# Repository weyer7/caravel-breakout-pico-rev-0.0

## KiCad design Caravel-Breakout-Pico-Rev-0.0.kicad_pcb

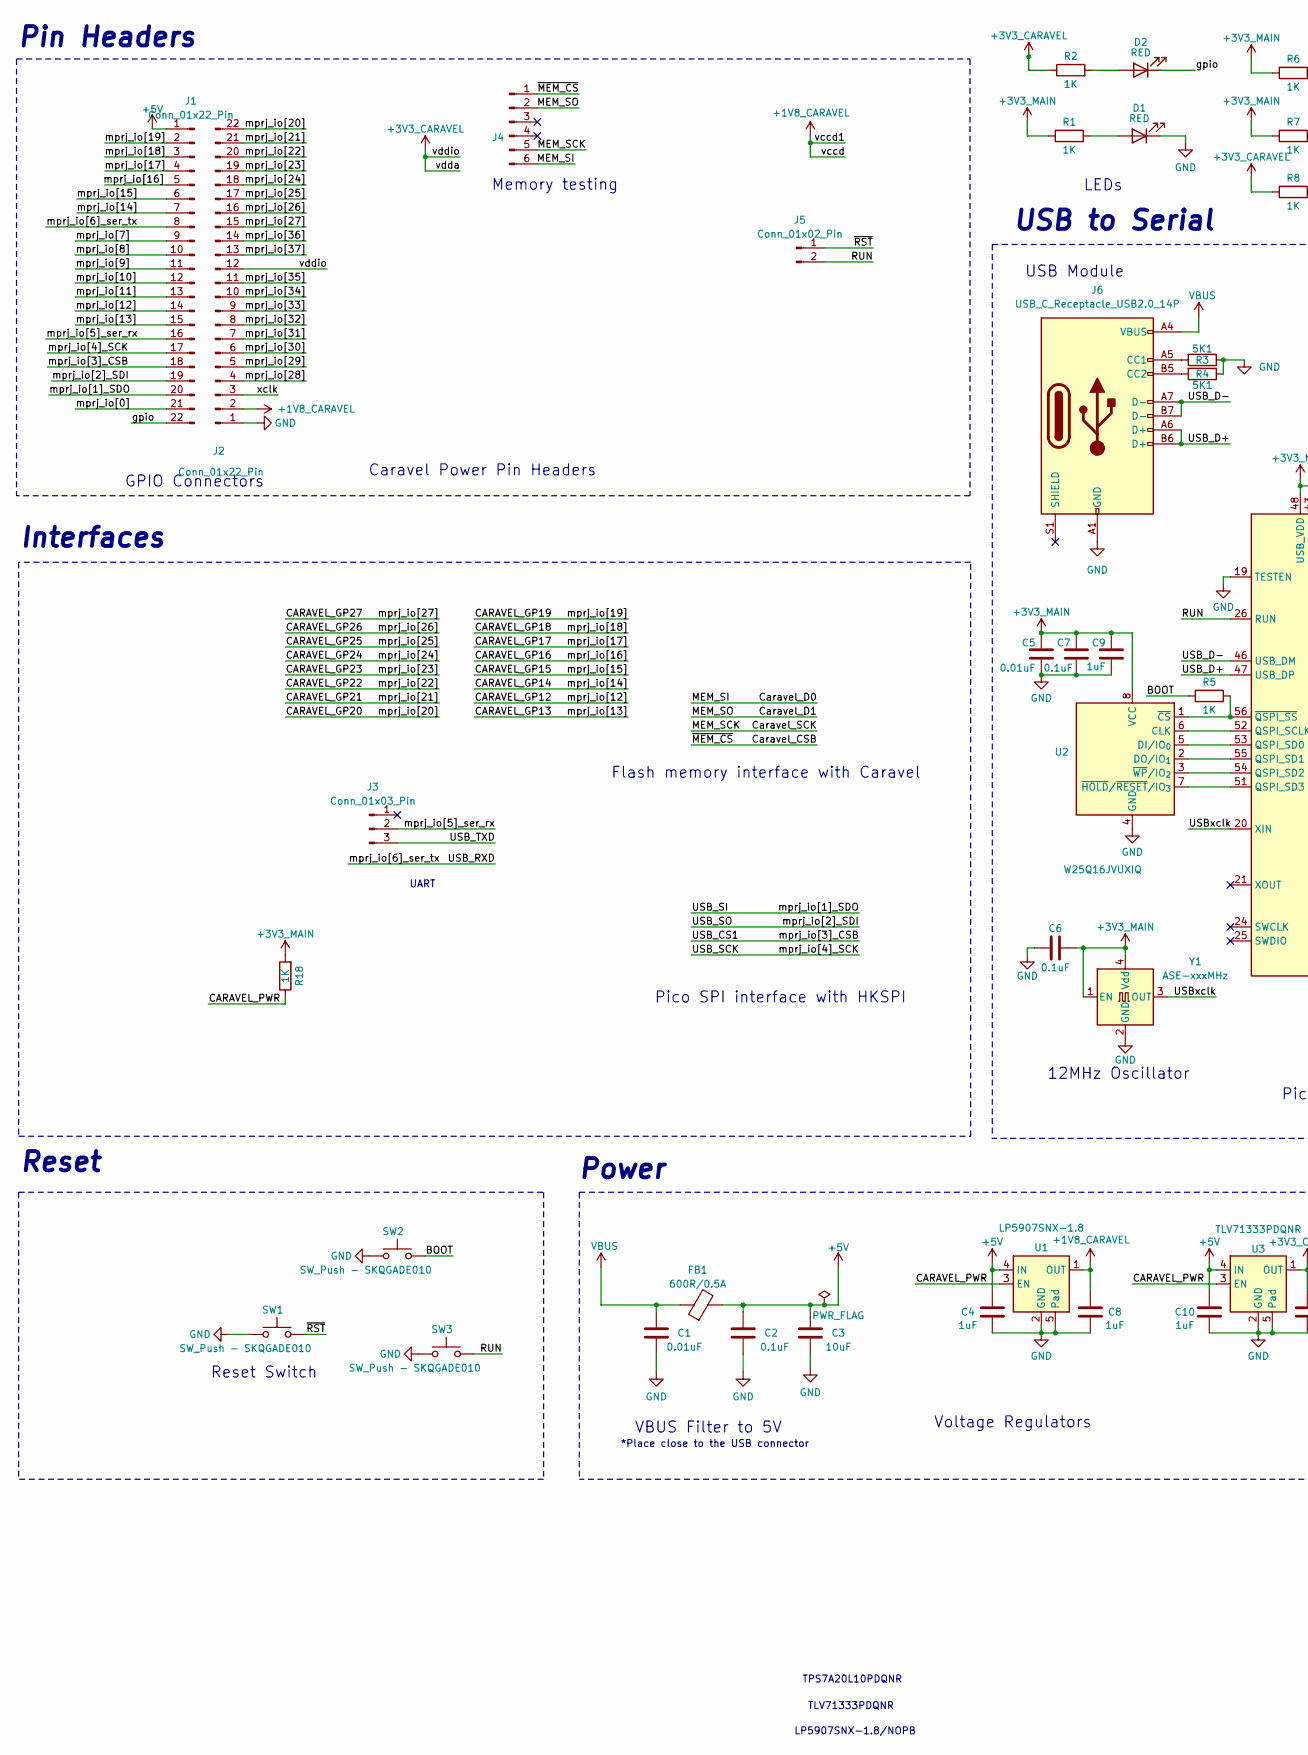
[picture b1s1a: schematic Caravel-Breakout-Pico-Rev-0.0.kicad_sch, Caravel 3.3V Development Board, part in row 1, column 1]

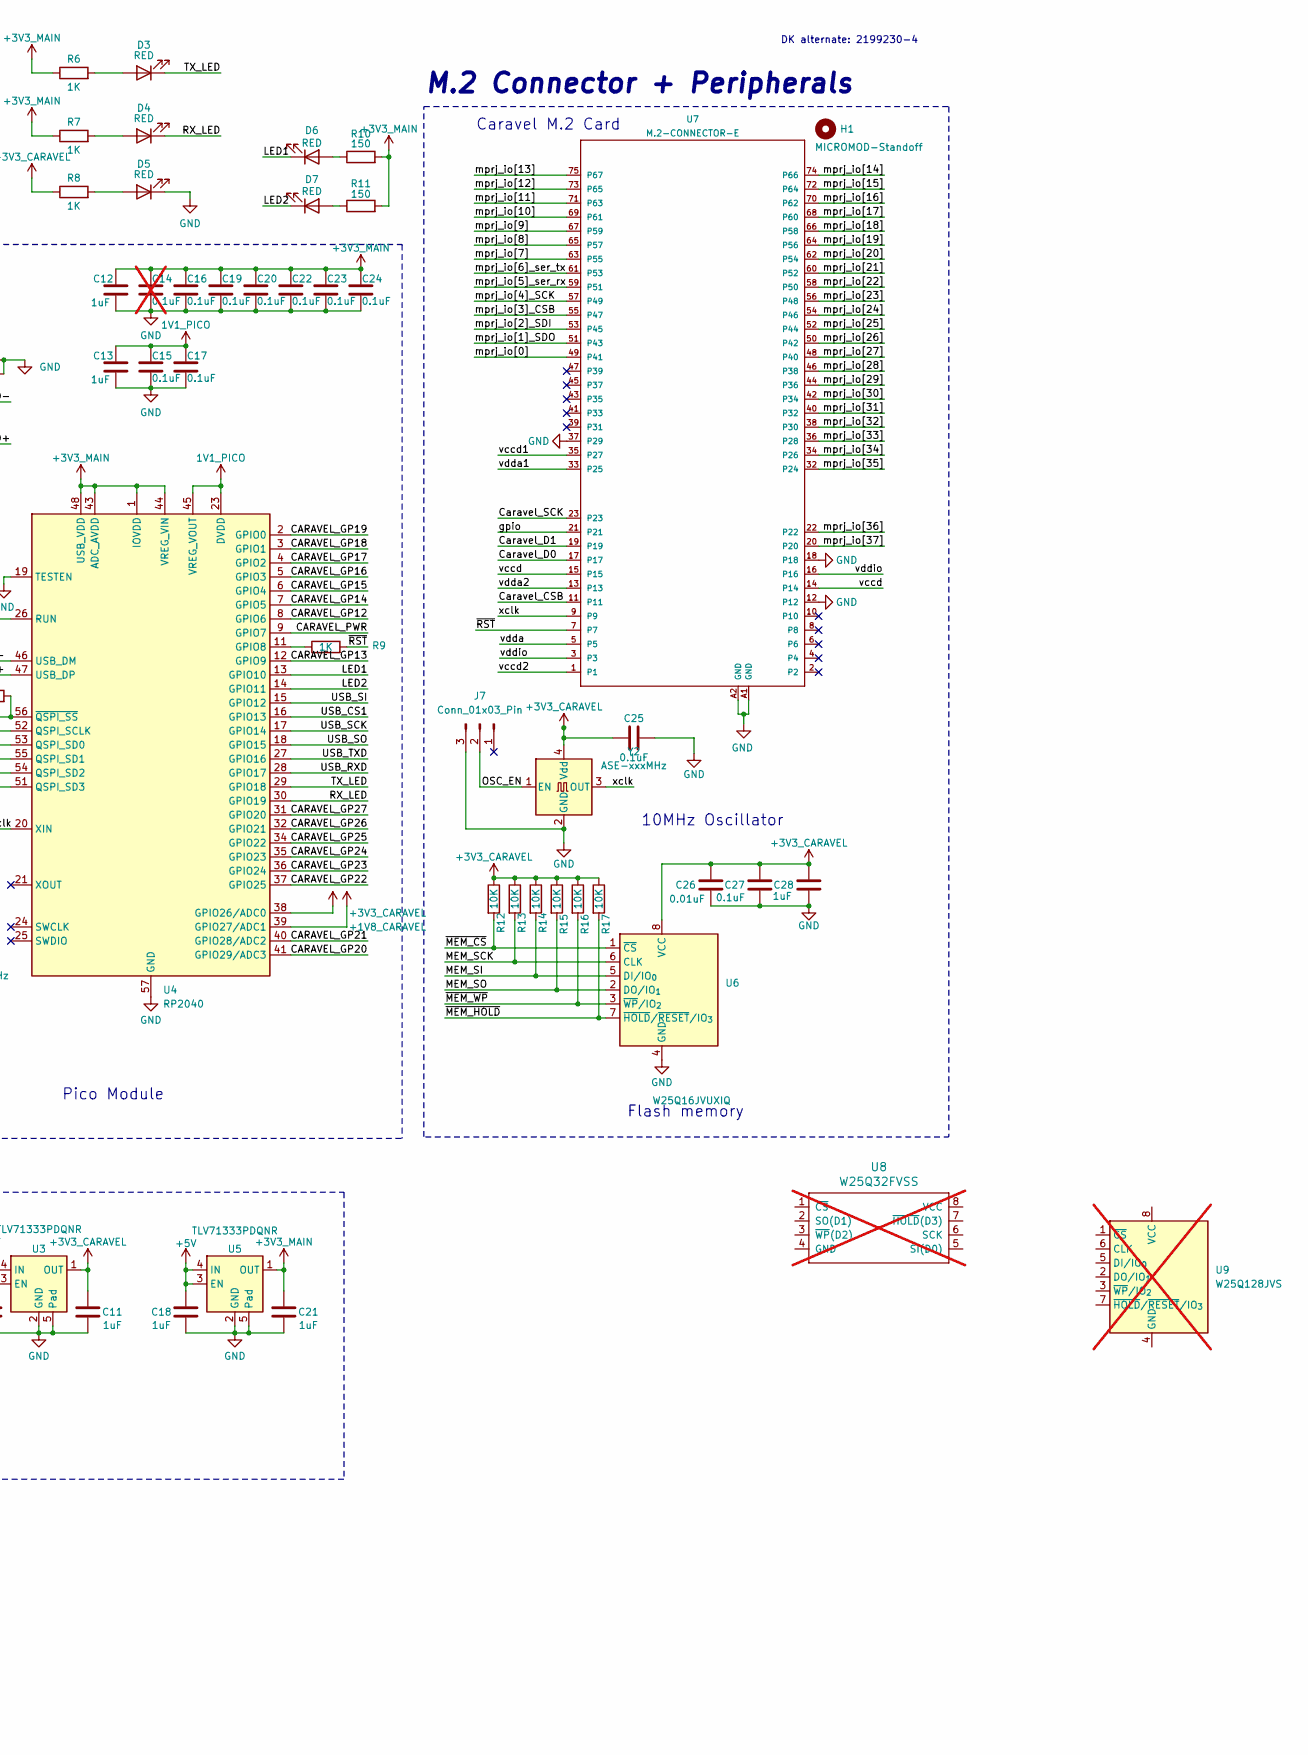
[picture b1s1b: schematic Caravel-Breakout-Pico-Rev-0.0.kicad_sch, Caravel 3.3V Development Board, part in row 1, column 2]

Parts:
C1, C5, C26: 0.01uF; C_0402_1005Metric; Part # C0805C103K5RAC7411
C2, C6, C7, C15, C16, C17, C19, C20, C22, C23, C24, C25, C27: 0.1uF; C_0402_1005Metric; Part # C0805C104K5RAC7411
C3: 10uF; C_0603_1608Metric; Part # CL21B106KAYQNNE
C4, C8, C9, C10, C11, C12, C13, C18, C21, C28: 1uF; C_0402_1005Metric; Part # 885012207103
C14: 0.1uF; C_0402_1005Metric; Part # C0805C104K5RAC7411; not fitted
D1, D2, D3, D4, D5, D6, D7: RED; LED_0603_1608Metric; Part # LTST-C230KRKT
FB1: 600R/0.5A; L_0805_2012Metric; Part # 7427920415
H1: MICROMOD-Standoff; MicroMod-Standoff
J1, J2: Conn_01x22_Pin; PinHeader_1x22_P2.54mm_Vertical
J3, J7: Conn_01x03_Pin; PinHeader_1x03_P1.27mm_Vertical
J4: Conn_01x06_Pin; PinHeader_1x06_P1.27mm_Vertical
J5: Conn_01x02_Pin; PinHeader_1x02_P2.54mm_Vertical
J6: USB_C_Receptacle_USB2.0_14P; USB_C_Receptacle_GCT_USB4105-xx-A_16P_TopMnt_Horizontal
R1, R2, R5, R6, R7, R8, R9, R18: 1K; R_0402_1005Metric; Part # RC0805FR-071KL
R3, R4: 5K1; R_0402_1005Metric
R10, R11: 150; R_0402_1005Metric; Part # RNCP0805FTD150R
R12, R13, R14, R15, R16, R17: 10K; R_0402_1005Metric; Part # RC0805FR-0710KL
SW1, SW2, SW3: SW_Push - SKQGADE010; SW4-SMD-5.2X5.2X1.5MM
U1: LP5907SNX-1.8; Texas_X2SON-4_1x1mm_P0.65mm
U2, U6: W25Q16JVUXIQ; USON-8_UX_2x3x0p6_WIN
U3, U5: TLV71333PDQNR; Texas_X2SON-4_1x1mm_P0.65mm
U4: RP2040; QFN-56-1EP_7x7mm_P0.4mm_EP3.2x3.2mm
U7: M.2-CONNECTOR-E
U8: W25Q32FVSS; SOIC127P790X216-8N; Part # W25Q32JVSSIQ; not fitted
U9: W25Q128JVS; SOIC-8_5.3x5.3mm_P1.27mm; not fitted
Y1, Y2: ASE-xxxMHz; Oscillator_SMD_Abracon_ASE-4Pin_3.2x2.5mm

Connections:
1V1_PICO: C13.1, C15.2, C17.2, U4.23 (DVDD), U4.45 (VREG_VOUT), U4.50 (DVDD)
+1V8_CARAVEL: C8.2, J2.2, U1.1 (OUT), U4.39 (GPIO27/ADC1), U7.14, U7.15, U7.35 (P27)
+3V3_CARAVEL: C11.2, C25.2, C26.2, C27.1, C28.1, J2.12, R2.1, R8.1, R12.1, R13.1, R14.1, R15.1, R16.1, R17.1, U3.1 (OUT), U4.38 (GPIO26/ADC0), U6.8 (VCC), U7.3, U7.5, U7.16, Y2.4 (Vdd)
+3V3_MAIN: C5.2, C6.1, C7.1, C9.1, C12.1, C14.2, C16.2, C19.2, C20.2, C21.2, C22.2, C23.2, C24.2, R1.1, R6.1, R7.1, R10.2, R11.2, R18.2, U2.8 (VCC), U4.1 (IOVDD), U4.10 (IOVDD), U4.22 (IOVDD), U4.33 (IOVDD), U4.42 (IOVDD), U4.43 (ADC_AVDD), U4.44 (VREG_VIN), U4.48 (USB_VDD), U4.49 (IOVDD), U5.1 (OUT), Y1.1 (EN), Y1.4 (Vdd)
+5V: C2.2, C3.2, C4.2, C10.2, C18.2, FB1.2, J1.1, U1.4 (IN), U3.4 (IN), U5.3 (EN), U5.4 (IN)
/BOOT: R5.1, SW2.1
/CARAVEL_GP12: J1.14, U4.8 (GPIO6), U7.73 (P65)
/CARAVEL_GP13: J1.15, U4.12 (GPIO9), U7.75 (P67)
/CARAVEL_GP14: J1.7, U4.7 (GPIO5), U7.74 (P66)
/CARAVEL_GP15: J1.6, U4.6 (GPIO4), U7.72 (P64)
/CARAVEL_GP16: J1.5, U4.5 (GPIO3), U7.70 (P62)
/CARAVEL_GP17: J1.4, U4.4 (GPIO2), U7.68 (P60)
/CARAVEL_GP18: J1.3, U4.3 (GPIO1), U7.66 (P58)
/CARAVEL_GP19: J1.2, U4.2 (GPIO0), U7.64 (P56)
/CARAVEL_GP20: J2.22, U4.41 (GPIO29/ADC3), U7.62 (P54)
/CARAVEL_GP21: J2.21, U4.40 (GPIO28/ADC2), U7.60 (P52)
/CARAVEL_GP22: J2.20, U4.37 (GPIO25), U7.58 (P50)
/CARAVEL_GP23: J2.19, U4.36 (GPIO24), U7.56 (P48)
/CARAVEL_GP24: J2.18, U4.35 (GPIO23), U7.54 (P46)
/CARAVEL_GP25: J2.17, U4.34 (GPIO22), U7.52 (P44)
/CARAVEL_GP26: J2.16, U4.32 (GPIO21), U7.50 (P42)
/CARAVEL_GP27: J2.15, U4.31 (GPIO20), U7.48 (P40)
/CARAVEL_PWR: R18.1, U1.3 (EN), U3.3 (EN), U4.9 (GPIO7)
/Caravel_CSB: J4.1, R12.2, U6.1 (~CS), U7.11
/Caravel_D0: J4.6, R14.2, U6.5 (DI/IO_{0}), U7.17
/Caravel_D1: J4.2, R15.2, U6.2 (DO/IO_{1}), U7.19
/Caravel_SCK: J4.5, R13.2, U6.6 (CLK), U7.23
/LED1: D6.1 (K), U4.13 (GPIO10)
/LED2: D7.1 (K), U4.14 (GPIO11)
/OSC_EN: J7.2, Y2.1 (EN)
/RUN: J5.2, SW3.1, U4.26 (RUN)
/RX_LED: D4.1 (K), U4.30 (GPIO19)
/TX_LED: D3.1 (K), U4.29 (GPIO18)
/USB_CS1: J1.18, U4.16 (GPIO13), U7.55 (P47)
/USB_D+: J6.A6 (D+), J6.B6 (D+), U4.47 (USB_DP)
/USB_D-: J6.A7 (D-), J6.B7 (D-), U4.46 (USB_DM)
/USB_RXD: J1.8, U4.28 (GPIO17), U7.61 (P53)
/USB_SCK: J1.17, U4.17 (GPIO14), U7.57 (P49)
/USB_SI: J1.20, U4.15 (GPIO12), U7.51 (P43)
/USB_SO: J1.19, U4.18 (GPIO15), U7.53 (P45)
/USB_TXD: J3.3, U4.27 (GPIO16)
/USBxclk: U4.20 (XIN), Y1.3 (OUT)
/gpio: D2.1 (K), J1.22, U7.21
/mprj_io[0]: J1.21, U7.49 (P41)
/mprj_io[5]_ser_rx: J1.16, J3.2, U7.59 (P51)
/mprj_io[7]: J1.9, U7.63 (P55)
/mprj_io[8]: J1.10, U7.65 (P57)
/mprj_io[9]: J1.11, U7.67 (P59)
/mprj_io[10]: J1.12, U7.69 (P61)
/mprj_io[11]: J1.13, U7.71 (P63)
/mprj_io[28]: J2.4, U7.46 (P38)
/mprj_io[29]: J2.5, U7.44 (P36)
/mprj_io[30]: J2.6, U7.42 (P34)
/mprj_io[31]: J2.7, U7.40 (P32)
/mprj_io[32]: J2.8, U7.38 (P30)
/mprj_io[33]: J2.9, U7.36 (P28)
/mprj_io[34]: J2.10, U7.34 (P26)
/mprj_io[35]: J2.11, U7.32 (P24)
/mprj_io[36]: J2.14, U7.22
/mprj_io[37]: J2.13, U7.20
/vccd2: U7.1
/vdda1: U7.33 (P25)
/vdda2: U7.13
/xclk: J2.3, U7.9, Y2.3 (OUT)
/~MEM_HOLD: R17.2, U6.7 (~HOLD/~RESET/IO_{3})
/~MEM_WP: R16.2, U6.3 (~WP/IO_{2})
/~RST: J5.1, R9.2, SW1.1, U7.7
GND: C1.2, C2.1, C3.1, C4.1, C5.1, C6.2, C7.2, C8.1, C9.2, C10.1, C11.1, C12.2, C13.2, C14.1, C15.1, C16.1, C17.1, C18.1, C19.1, C20.1, C21.1, C22.1, C23.1, C24.1, C25.1, C26.1, C27.2, C28.2, D1.1 (K), D5.1 (K), J2.1, J6.A1 (GND), J6.A12 (GND), J6.B1 (GND), J6.B12 (GND), J7.3, R3.1, R4.1, SW1.2, SW2.2, SW3.2, U1.2 (GND), U1.5 (Pad), U2.4 (GND), U3.2 (GND), U3.5 (Pad), U4.19 (TESTEN), U4.57 (GND), U5.2 (GND), U5.5 (Pad), U6.4 (GND), U7.12, U7.18, U7.37 (P29), U7.A1 (GND), U7.A2 (GND), Y1.2 (GND), Y2.2 (GND)
unnamed: D1.2 (A), R1.2
unnamed: D2.2 (A), R2.2
unnamed: D3.2 (A), R6.2
unnamed: D4.2 (A), R7.2
unnamed: D5.2 (A), R8.2
unnamed: D6.2 (A), R10.1
unnamed: D7.2 (A), R11.1
unnamed: J6.A5 (CC1), R3.2
unnamed: J6.B5 (CC2), R4.2
unnamed: U2.6 (CLK), U4.52 (QSPI_SCLK)
unnamed: U2.5 (DI/IO_{0}), U4.53 (QSPI_SD0)
unnamed: U2.2 (DO/IO_{1}), U4.55 (QSPI_SD1)
unnamed: R5.2, U2.1 (~CS), U4.56 (~QSPI_SS)
unnamed: U2.7 (~HOLD/~RESET/IO_{3}), U4.51 (QSPI_SD3)
unnamed: U2.3 (~WP/IO_{2}), U4.54 (QSPI_SD2)
unnamed: R9.1, U4.11 (GPIO8)
VBUS: C1.1, FB1.1, J6.A4 (VBUS), J6.A9 (VBUS), J6.B4 (VBUS), J6.B9 (VBUS)

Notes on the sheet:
USB to Serial
USB Module
10MHz Oscillator
*Place close to the USB connector
Flash memory interface with Caravel
TPS7A20L10PDQNR
Caravel Power Pin Headers
GPIO Connectors
LEDs
Flash memory
TLV71333PDQNR
M.2 Connector + Peripherals
12MHz Oscillator
Power
Pin Headers
VBUS Filter to 5V
UART
LP5907SNX-1.8/NOPB
Interfaces
Voltage Regulators
Reset Switch
DK alternate: 2199230-4
Memory testing
Pico SPI interface with HKSPI
Pico Module
Reset
Caravel M.2 Card

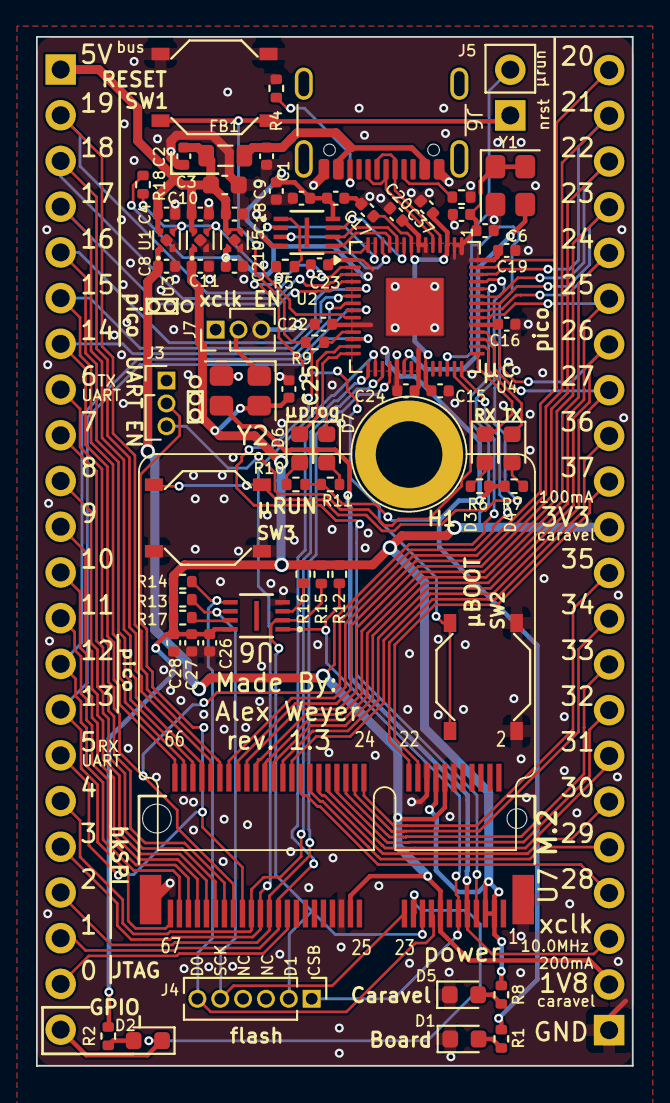
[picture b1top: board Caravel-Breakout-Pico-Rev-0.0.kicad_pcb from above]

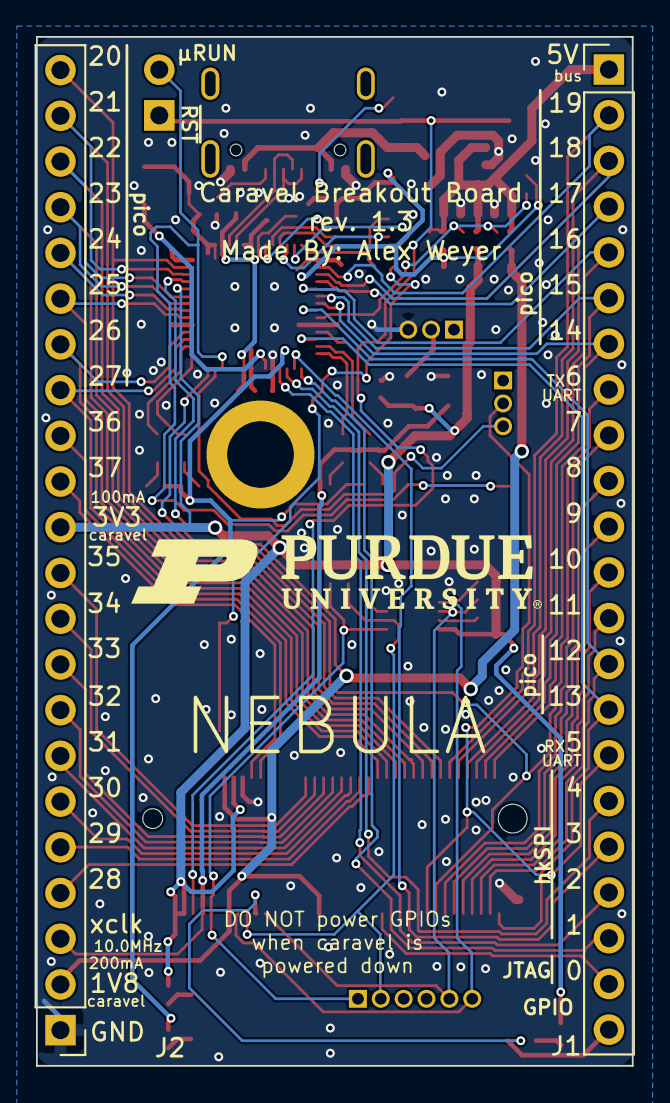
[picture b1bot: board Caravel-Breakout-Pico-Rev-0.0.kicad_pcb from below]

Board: 4 copper layers, 33.1 x 57.2 mm, 73 parts (2 on the bottom side), 82 nets.

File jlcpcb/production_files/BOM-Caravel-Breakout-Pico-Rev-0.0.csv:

Comment,Designator,Footprint,LCSC,Quantity
0.01uF,"C1,C26,C5",C_0402_1005Metric,C15195,3
0.1uF,"C15,C16,C17,C19,C2,C20,C22,C23,C24,C25,C27,C6,C7",C_0402_1005Metric,C1525,13
10K,"R12,R13,R14,R15,R16,R17",R_0402_1005Metric,C25744,6
10uF,C3,C_0603_1608Metric,C19702,1
150,"R10,R11",R_0402_1005Metric,C25082,2
1K,"R1,R18,R2,R5,R6,R7,R8,R9",R_0402_1005Metric,C11702,8
1uF,"C10,C11,C12,C13,C18,C21,C28,C4,C8,C9",C_0402_1005Metric,C52923,10
5K1,"R3,R4",R_0402_1005Metric,C25905,2
600R/0.5A,FB1,L_0805_2012Metric,C1017,1
ASE-xxxMHz,Y2,Oscillator_SMD_Abracon_ASE-4Pin_3.2x2.5mm,C2901558,1
ASE-xxxMHz,Y1,Oscillator_SMD_Abracon_ASE-4Pin_3.2x2.5mm,C2901561,1
LP5907SNX-1.8,U1,Texas_X2SON-4_1x1mm_P0.65mm,C139378,1
M.2-CONNECTOR-E,U7,M.2-CONNECTOR-E,C7498141,1
MICROMOD-Standoff,H1,MicroMod-Standoff,C7496631,1
RED,"D1,D2,D3,D4,D5,D6,D7",LED_0603_1608Metric,C2286,7
RP2040,U4,QFN-56-1EP_7x7mm_P0.4mm_EP3.2x3.2mm,C2040,1
SW_Push - SKQGADE010,"SW1,SW2,SW3",SW4-SMD-5.2X5.2X1.5MM,C318884,3
TLV71333PDQNR,"U3,U5",Texas_X2SON-4_1x1mm_P0.65mm,C2867340,2
USB_C_Receptacle_USB2.0_14P,J6,USB_C_Receptacle_GCT_USB4105-xx-A_16P_TopMnt_Horizontal,C2988369,1
W25Q16JVUXIQ,"U2,U6",USON-8_UX_2x3x0p6_WIN,C2843335,2
Conn_01x02_Pin,J5,PinHeader_1x02_P2.54mm_Vertical,,1
Conn_01x06_Pin,J4,PinHeader_1x06_P1.27mm_Vertical,,1
Conn_01x03_Pin,J7,PinHeader_1x03_P1.27mm_Vertical,,1
Conn_01x03_Pin,J3,PinHeader_1x03_P1.27mm_Vertical,,1
Conn_01x22_Pin,J2,PinHeader_1x22_P2.54mm_Vertical,,1
Conn_01x22_Pin,J1,PinHeader_1x22_P2.54mm_Vertical,,1
